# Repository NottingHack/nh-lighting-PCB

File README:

PCB for nh-lighting

https://wiki.nottinghack.org.uk/wiki/Lighting_Automation

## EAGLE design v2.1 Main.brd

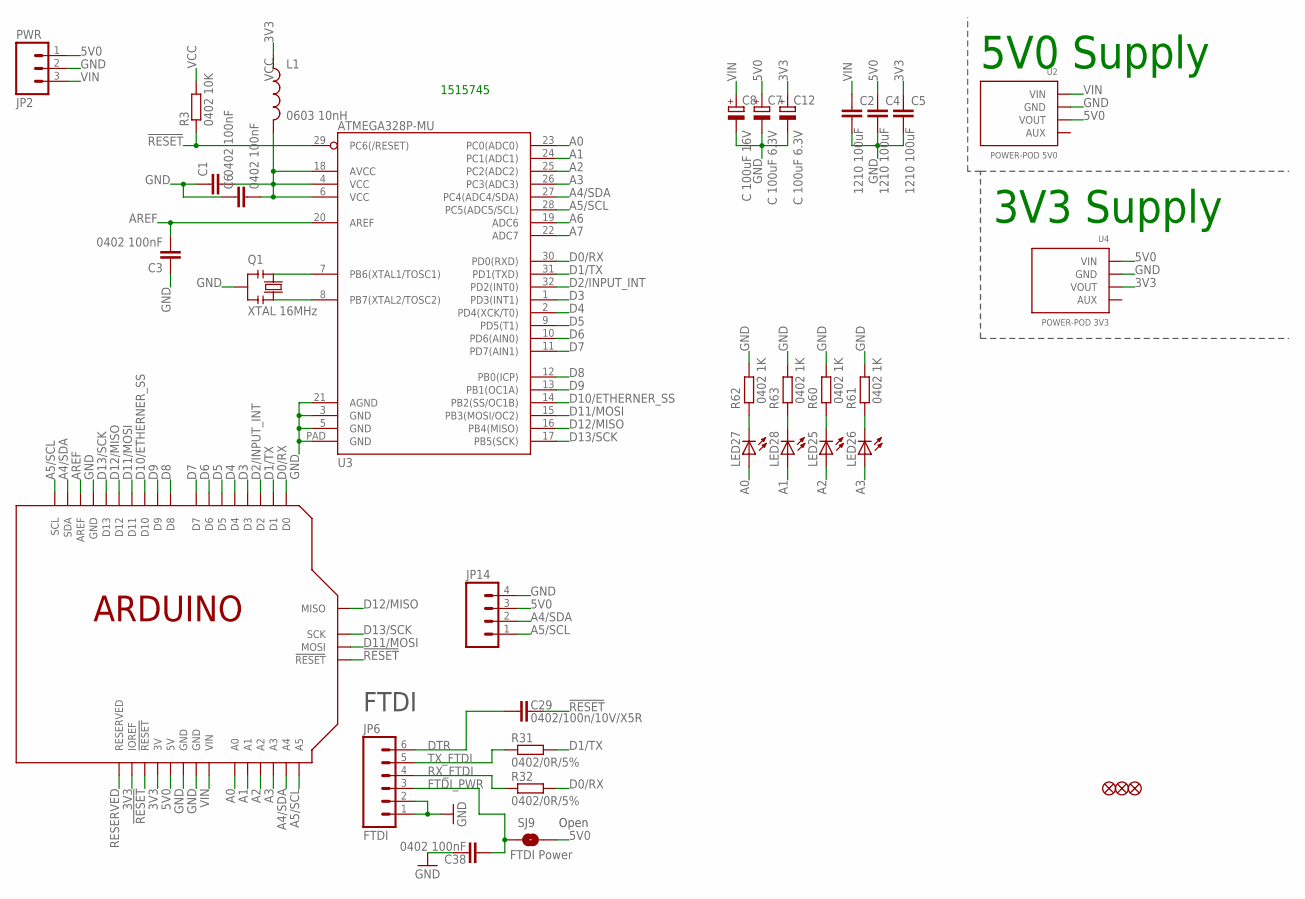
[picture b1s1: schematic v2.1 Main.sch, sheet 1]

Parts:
C1, C3, C6, C38: 0402 100nF; C0402-SMALLER
C2, C4, C5: 1210 100uF; C1210
C7, C12: C 100uF 6.3V; PANASONIC_C
C8: C 100uF 16V; PANASONIC_C
C29: 0402/100n/10V/X5R; C0402-ARDUINO-ROUND
JP2: PWR; SCREWTERMINAL-5MM-3
JP4, JP7, JP9: FIDUCIAL1X2.5-STOP; FIDUCIAL-1X2.5-STOP
JP6: FTDI; 1X06
JP14: M04PTH; 1X04
L1: 0603 10nH; C0603K-SMALL
LED25, LED26, LED27, LED28: LED0805-1206; LED-0805-1206
Q1: XTAL 16MHz; RESONATOR
R3: 0402 10K; R0402-SMALLER
R31, R32: 0402/0R/5%; R0402-ARDUINO-ROUND
R60, R61, R62, R63: 0402 1K; R0402-SMALLER
SJ9: FTDI Power; SJ_2S-TRACE
U1: ARDUINOSPI-REFRENCE; ARDUINOR3-LWKTXT-REF-SPI
U2: POWER-POD 5V0; POWER-POD-LANDING
U3: ATMEGA328P-MU; MLF32-SHORT-CREAM
U4: POWER-POD 3V3; POWER-POD-LANDING

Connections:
3V3: C5.1, C12.+, L1.1, U1.3V, U1.IOREF, U4.3 (VOUT)
5V0: C4.1, C7.+, JP2.1, JP14.3, SJ9.2, U1.5V, U1.5V@ISP (5V), U2.3 (VOUT), U4.1 (VIN); also elsewhere on the board
!RESET: C29.1, R3.1, U1.!RESET, U1.!RESET@ISP (!RESET), U3.29 (PC6(/RESET))
A0: LED27.A, U1.A0, U3.23 (PC0(ADC0))
A1: LED28.A, U1.A1, U3.24 (PC1(ADC1))
A2: LED25.A, U1.A2, U3.25 (PC2(ADC2))
A3: LED26.A, U1.A3, U3.26 (PC3(ADC3))
A4/SDA: JP14.2, U1.A4, U1.SDA, U3.27 (PC4(ADC4/SDA)); also elsewhere on the board
A5/SCL: JP14.1, U1.A5, U1.SCL, U3.28 (PC5(ADC5/SCL)); also elsewhere on the board
A6: U3.19 (ADC6)
A7: U3.22 (ADC7)
AREF: C3.2, U1.AREF, U3.20 (AREF)
D0/RX: R32.2, U1.D0, U3.30 (PD0(RXD))
D1/TX: R31.2, U1.D1, U3.31 (PD1(TXD))
D2/INPUT_INT: U1.D2, U3.32 (PD2(INT0)); also elsewhere on the board
D3: U1.D3, U3.1 (PD3(INT1))
D4: U1.D4, U3.2 (PD4(XCK/T0))
D5: U1.D5, U3.9 (PD5(T1))
D6: U1.D6, U3.10 (PD6(AIN0))
D7: U1.D7, U3.11 (PD7(AIN1))
D8: U1.D8, U3.12 (PB0(ICP))
D9: U1.D9, U3.13 (PB1(OC1A))
D10/ETHERNER_SS: U1.D10, U3.14 (PB2(SS/OC1B))
D11/MOSI: U1.D11, U1.MOSI, U3.15 (PB3(MOSI/OC2))
D12/MISO: U1.D12, U1.MISO, U3.16 (PB4(MISO))
D13/SCK: U1.D13, U1.SCK, U3.17 (PB5(SCK))
DTR: C29.2, JP6.6
FTDI_PWR: C38.2, JP6.3, SJ9.1
GND: C1.1, C2.2, C3.1, C4.2, C5.2, C6.1, C7.-, C8.-, C12.-, C38.1, JP2.2, JP6.1, JP6.2, JP14.4, Q1.2, R60.2, R61.2, R62.2, R63.2, U1.GND@1 (GND), U1.GND@2 (GND), U1.GND@3 (GND), U1.GND@ISP (GND), U2.2 (GND), U3.3 (GND), U3.5 (GND), U3.21 (AGND), U3.PAD (GND), U4.2 (GND); also elsewhere on the board
unnamed: Q1.1, U3.7 (PB6(XTAL1/TOSC1))
unnamed: Q1.3, U3.8 (PB7(XTAL2/TOSC2))
unnamed: LED27.C, R62.1
unnamed: LED28.C, R63.1
unnamed: LED25.C, R60.1
unnamed: LED26.C, R61.1
RESERVED: U1.RESERVED
RX_FTDI: JP6.4, R32.1
TX_FTDI: JP6.5, R31.1
VCC: C1.2, C6.2, L1.2, R3.2, U3.4 (VCC), U3.6 (VCC), U3.18 (AVCC)
VIN: C2.1, C8.+, JP2.3, U1.VIN, U2.1 (VIN)

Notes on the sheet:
FTDI
Open
1515745
5V0 Supply
3V3 Supply

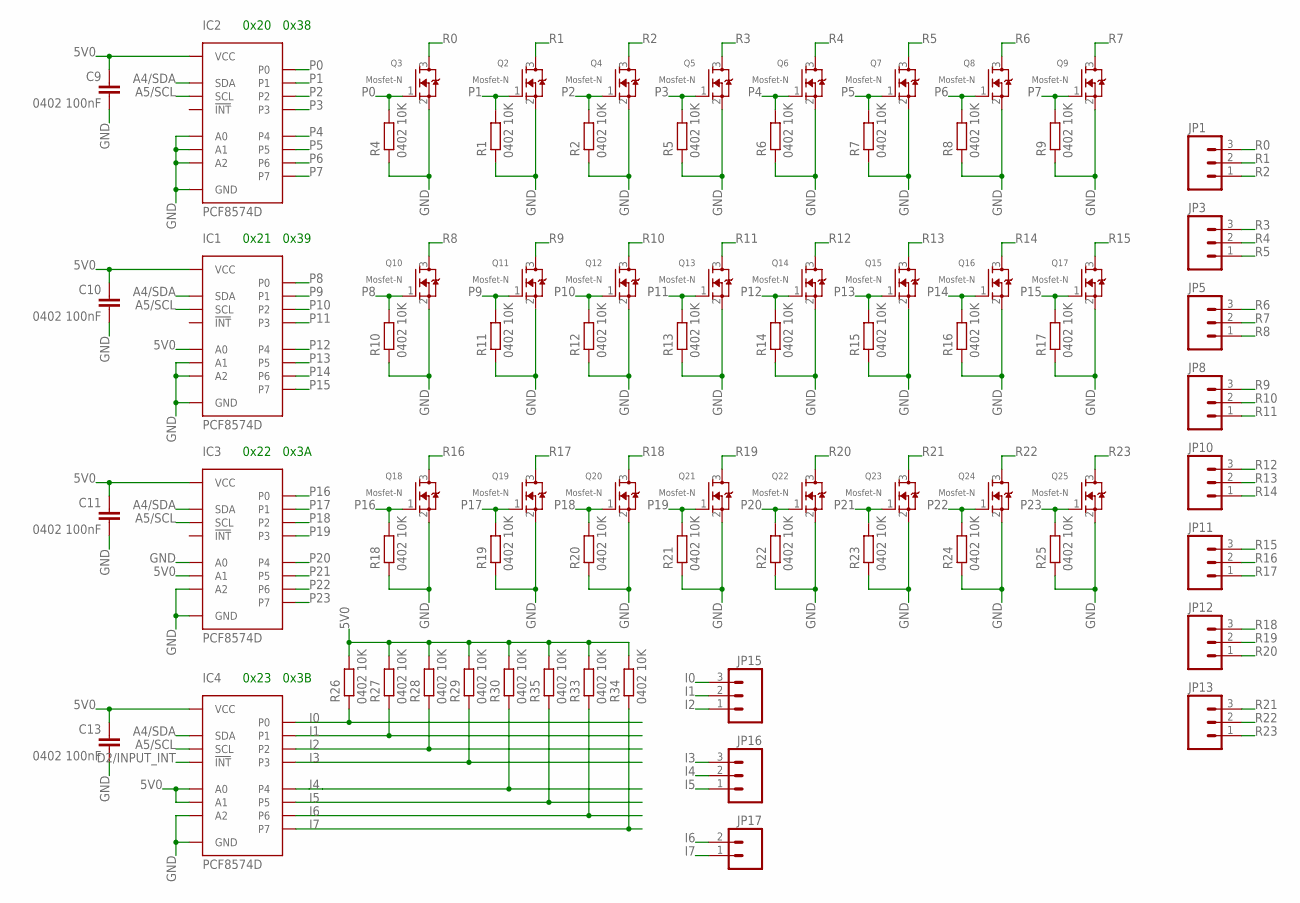
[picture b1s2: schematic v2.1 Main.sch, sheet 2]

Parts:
C9, C10, C11, C13: 0402 100nF; C0402-SMALLER
IC1, IC2, IC3, IC4: PCF8574D; SO16-7.5MM
JP1, JP3, JP5, JP8, JP10, JP11, JP12, JP13, JP15, JP16: M03-SCREW-5MM; SCREWTERMINAL-5MM-3
JP17: M025MM; SCREWTERMINAL-5MM-2
Q2, Q3, Q4, Q5, Q6, Q7, Q8, Q9, Q10, Q11, Q12, Q13, Q14, Q15, Q16, Q17, Q18, Q19, Q20, Q21, Q22, Q23, Q24, Q25: Mosfet-N; SOT23-3
R1, R2, R4, R5, R6, R7, R8, R9, R10, R11, R12, R13, R14, R15, R16, R17, R18, R19, R20, R21, R22, R23, R24, R25, R26, R27, R28, R29, R30, R33, R34, R35: 0402 10K; R0402-SMALLER

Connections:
5V0: C9.1, C10.1, C11.1, C13.1, IC1.1 (A0), IC1.16 (VCC), IC2.16 (VCC), IC3.2 (A1), IC3.16 (VCC), IC4.1 (A0), IC4.2 (A1), IC4.16 (VCC), R26.2, R27.2, R28.2, R29.2, R30.2, R33.2, R34.2, R35.2; also elsewhere on the board
A4/SDA: IC1.15 (SDA), IC2.15 (SDA), IC3.15 (SDA), IC4.15 (SDA); also elsewhere on the board
A5/SCL: IC1.14 (SCL), IC2.14 (SCL), IC3.14 (SCL), IC4.14 (SCL); also elsewhere on the board
D2/INPUT_INT: IC4.13 (!INT); also elsewhere on the board
GND: C9.2, C10.2, C11.2, C13.2, IC1.2 (A1), IC1.3 (A2), IC1.8 (GND), IC2.1 (A0), IC2.2 (A1), IC2.3 (A2), IC2.8 (GND), IC3.1 (A0), IC3.3 (A2), IC3.8 (GND), IC4.3 (A2), IC4.8 (GND), Q2.2 (S), Q3.2 (S), Q4.2 (S), Q5.2 (S), Q6.2 (S), Q7.2 (S), Q8.2 (S), Q9.2 (S), Q10.2 (S), Q11.2 (S), Q12.2 (S), Q13.2 (S), Q14.2 (S), Q15.2 (S), Q16.2 (S), Q17.2 (S), Q18.2 (S), Q19.2 (S), Q20.2 (S), Q21.2 (S), Q22.2 (S), Q23.2 (S), Q24.2 (S), Q25.2 (S), R1.1, R2.1, R4.1, R5.1, R6.1, R7.1, R8.1, R9.1, R10.1, R11.1, R12.1, R13.1, R14.1, R15.1, R16.1, R17.1, R18.1, R19.1, R20.1, R21.1, R22.1, R23.1, R24.1, R25.1; also elsewhere on the board
I0: IC4.4 (P0), JP15.3, R26.1
I1: IC4.5 (P1), JP15.2, R27.1
I2: IC4.6 (P2), JP15.1, R28.1
I3: IC4.7 (P3), JP16.3, R29.1
I4: IC4.9 (P4), JP16.2, R30.1
I5: IC4.10 (P5), JP16.1, R35.1
I6: IC4.11 (P6), JP17.2, R33.1
I7: IC4.12 (P7), JP17.1, R34.1
P0: IC2.4 (P0), Q3.1 (G), R4.2; also elsewhere on the board
P1: IC2.5 (P1), Q2.1 (G), R1.2; also elsewhere on the board
P2: IC2.6 (P2), Q4.1 (G), R2.2; also elsewhere on the board
P3: IC2.7 (P3), Q5.1 (G), R5.2; also elsewhere on the board
P4: IC2.9 (P4), Q6.1 (G), R6.2; also elsewhere on the board
P5: IC2.10 (P5), Q7.1 (G), R7.2; also elsewhere on the board
P6: IC2.11 (P6), Q8.1 (G), R8.2; also elsewhere on the board
P7: IC2.12 (P7), Q9.1 (G), R9.2; also elsewhere on the board
P8: IC1.4 (P0), Q10.1 (G), R10.2; also elsewhere on the board
P9: IC1.5 (P1), Q11.1 (G), R11.2; also elsewhere on the board
P10: IC1.6 (P2), Q12.1 (G), R12.2; also elsewhere on the board
P11: IC1.7 (P3), Q13.1 (G), R13.2; also elsewhere on the board
P12: IC1.9 (P4), Q14.1 (G), R14.2; also elsewhere on the board
P13: IC1.10 (P5), Q15.1 (G), R15.2; also elsewhere on the board
P14: IC1.11 (P6), Q16.1 (G), R16.2; also elsewhere on the board
P15: IC1.12 (P7), Q17.1 (G), R17.2; also elsewhere on the board
P16: IC3.4 (P0), Q18.1 (G), R18.2; also elsewhere on the board
P17: IC3.5 (P1), Q19.1 (G), R19.2; also elsewhere on the board
P18: IC3.6 (P2), Q20.1 (G), R20.2; also elsewhere on the board
P19: IC3.7 (P3), Q21.1 (G), R21.2; also elsewhere on the board
P20: IC3.9 (P4), Q22.1 (G), R22.2; also elsewhere on the board
P21: IC3.10 (P5), Q23.1 (G), R23.2; also elsewhere on the board
P22: IC3.11 (P6), Q24.1 (G), R24.2; also elsewhere on the board
P23: IC3.12 (P7), Q25.1 (G), R25.2; also elsewhere on the board
R0: JP1.3, Q3.3 (D)
R1: JP1.2, Q2.3 (D)
R2: JP1.1, Q4.3 (D)
R3: JP3.3, Q5.3 (D)
R4: JP3.2, Q6.3 (D)
R5: JP3.1, Q7.3 (D)
R6: JP5.3, Q8.3 (D)
R7: JP5.2, Q9.3 (D)
R8: JP5.1, Q10.3 (D)
R9: JP8.3, Q11.3 (D)
R10: JP8.2, Q12.3 (D)
R11: JP8.1, Q13.3 (D)
R12: JP10.3, Q14.3 (D)
R13: JP10.2, Q15.3 (D)
R14: JP10.1, Q16.3 (D)
R15: JP11.3, Q17.3 (D)
R16: JP11.2, Q18.3 (D)
R17: JP11.1, Q19.3 (D)
R18: JP12.3, Q20.3 (D)
R19: JP12.2, Q21.3 (D)
R20: JP12.1, Q22.3 (D)
R21: JP13.3, Q23.3 (D)
R22: JP13.2, Q24.3 (D)
R23: JP13.1, Q25.3 (D)

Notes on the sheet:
0x20
0x21
0x22
0x23
0x38
0x39
0x3A
0x3B

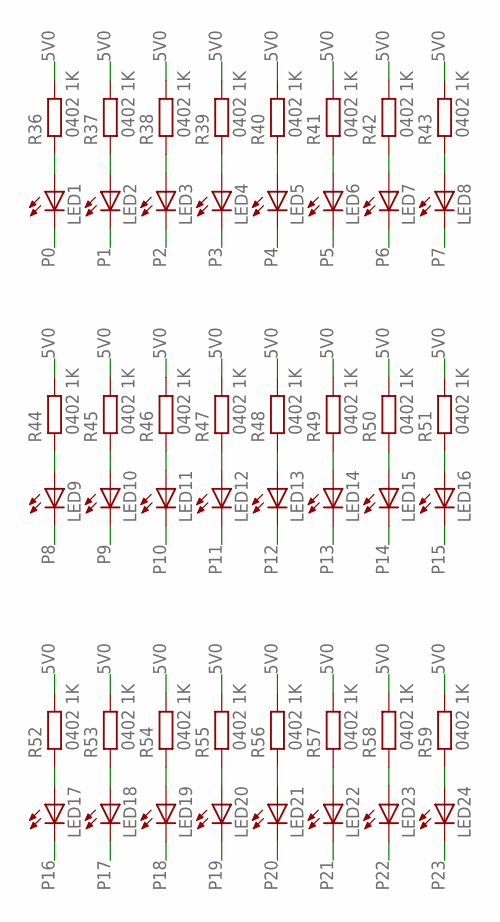
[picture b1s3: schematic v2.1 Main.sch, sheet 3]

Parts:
LED1, LED2, LED3, LED4, LED5, LED6, LED7, LED8, LED9, LED10, LED11, LED12, LED13, LED14, LED15, LED16, LED17, LED18, LED19, LED20, LED21, LED22, LED23, LED24: LED0805-1206; LED-0805-1206
R36, R37, R38, R39, R40, R41, R42, R43, R44, R45, R46, R47, R48, R49, R50, R51, R52, R53, R54, R55, R56, R57, R58, R59: 0402 1K; R0402-SMALLER

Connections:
5V0: R36.2, R37.2, R38.2, R39.2, R40.2, R41.2, R42.2, R43.2, R44.2, R45.2, R46.2, R47.2, R48.2, R49.2, R50.2, R51.2, R52.2, R53.2, R54.2, R55.2, R56.2, R57.2, R58.2, R59.2; also elsewhere on the board
unnamed: LED1.A, R36.1
unnamed: LED2.A, R37.1
unnamed: LED3.A, R38.1
unnamed: LED4.A, R39.1
unnamed: LED5.A, R40.1
unnamed: LED6.A, R41.1
unnamed: LED7.A, R42.1
unnamed: LED8.A, R43.1
unnamed: LED9.A, R44.1
unnamed: LED10.A, R45.1
unnamed: LED11.A, R46.1
unnamed: LED12.A, R47.1
unnamed: LED13.A, R48.1
unnamed: LED14.A, R49.1
unnamed: LED15.A, R50.1
unnamed: LED16.A, R51.1
unnamed: LED17.A, R52.1
unnamed: LED18.A, R53.1
unnamed: LED19.A, R54.1
unnamed: LED20.A, R55.1
unnamed: LED21.A, R56.1
unnamed: LED22.A, R57.1
unnamed: LED23.A, R58.1
unnamed: LED24.A, R59.1
P0: LED1.C; also elsewhere on the board
P1: LED2.C; also elsewhere on the board
P2: LED3.C; also elsewhere on the board
P3: LED4.C; also elsewhere on the board
P4: LED5.C; also elsewhere on the board
P5: LED6.C; also elsewhere on the board
P6: LED7.C; also elsewhere on the board
P7: LED8.C; also elsewhere on the board
P8: LED9.C; also elsewhere on the board
P9: LED10.C; also elsewhere on the board
P10: LED11.C; also elsewhere on the board
P11: LED12.C; also elsewhere on the board
P12: LED13.C; also elsewhere on the board
P13: LED14.C; also elsewhere on the board
P14: LED15.C; also elsewhere on the board
P15: LED16.C; also elsewhere on the board
P16: LED17.C; also elsewhere on the board
P17: LED18.C; also elsewhere on the board
P18: LED19.C; also elsewhere on the board
P19: LED20.C; also elsewhere on the board
P20: LED21.C; also elsewhere on the board
P21: LED22.C; also elsewhere on the board
P22: LED23.C; also elsewhere on the board
P23: LED24.C; also elsewhere on the board

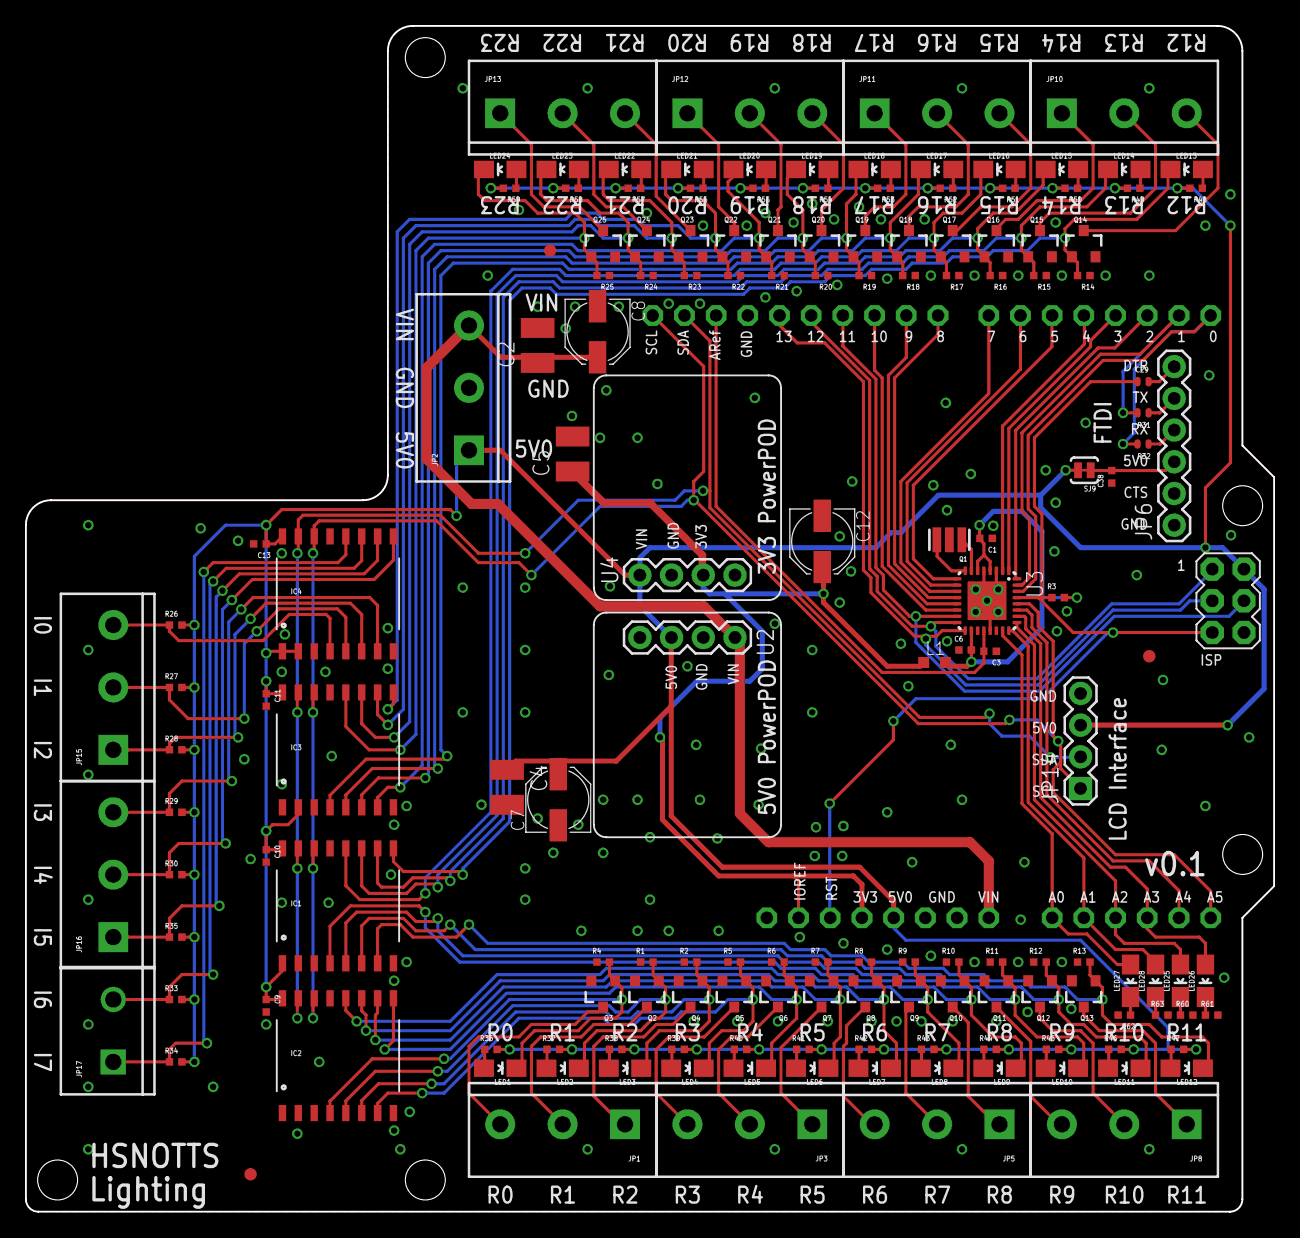
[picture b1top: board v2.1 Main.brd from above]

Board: 2 copper layers, 100.0 x 95.0 mm, 158 parts (0 on the bottom side), 117 nets.

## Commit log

2018-07-11 nh-lighting PCBs

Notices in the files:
parts and their libraries:
SparkFunJan12: Licensing: CC v3.0 Share-Alike You are welcome to use this library for commercial purposes.
